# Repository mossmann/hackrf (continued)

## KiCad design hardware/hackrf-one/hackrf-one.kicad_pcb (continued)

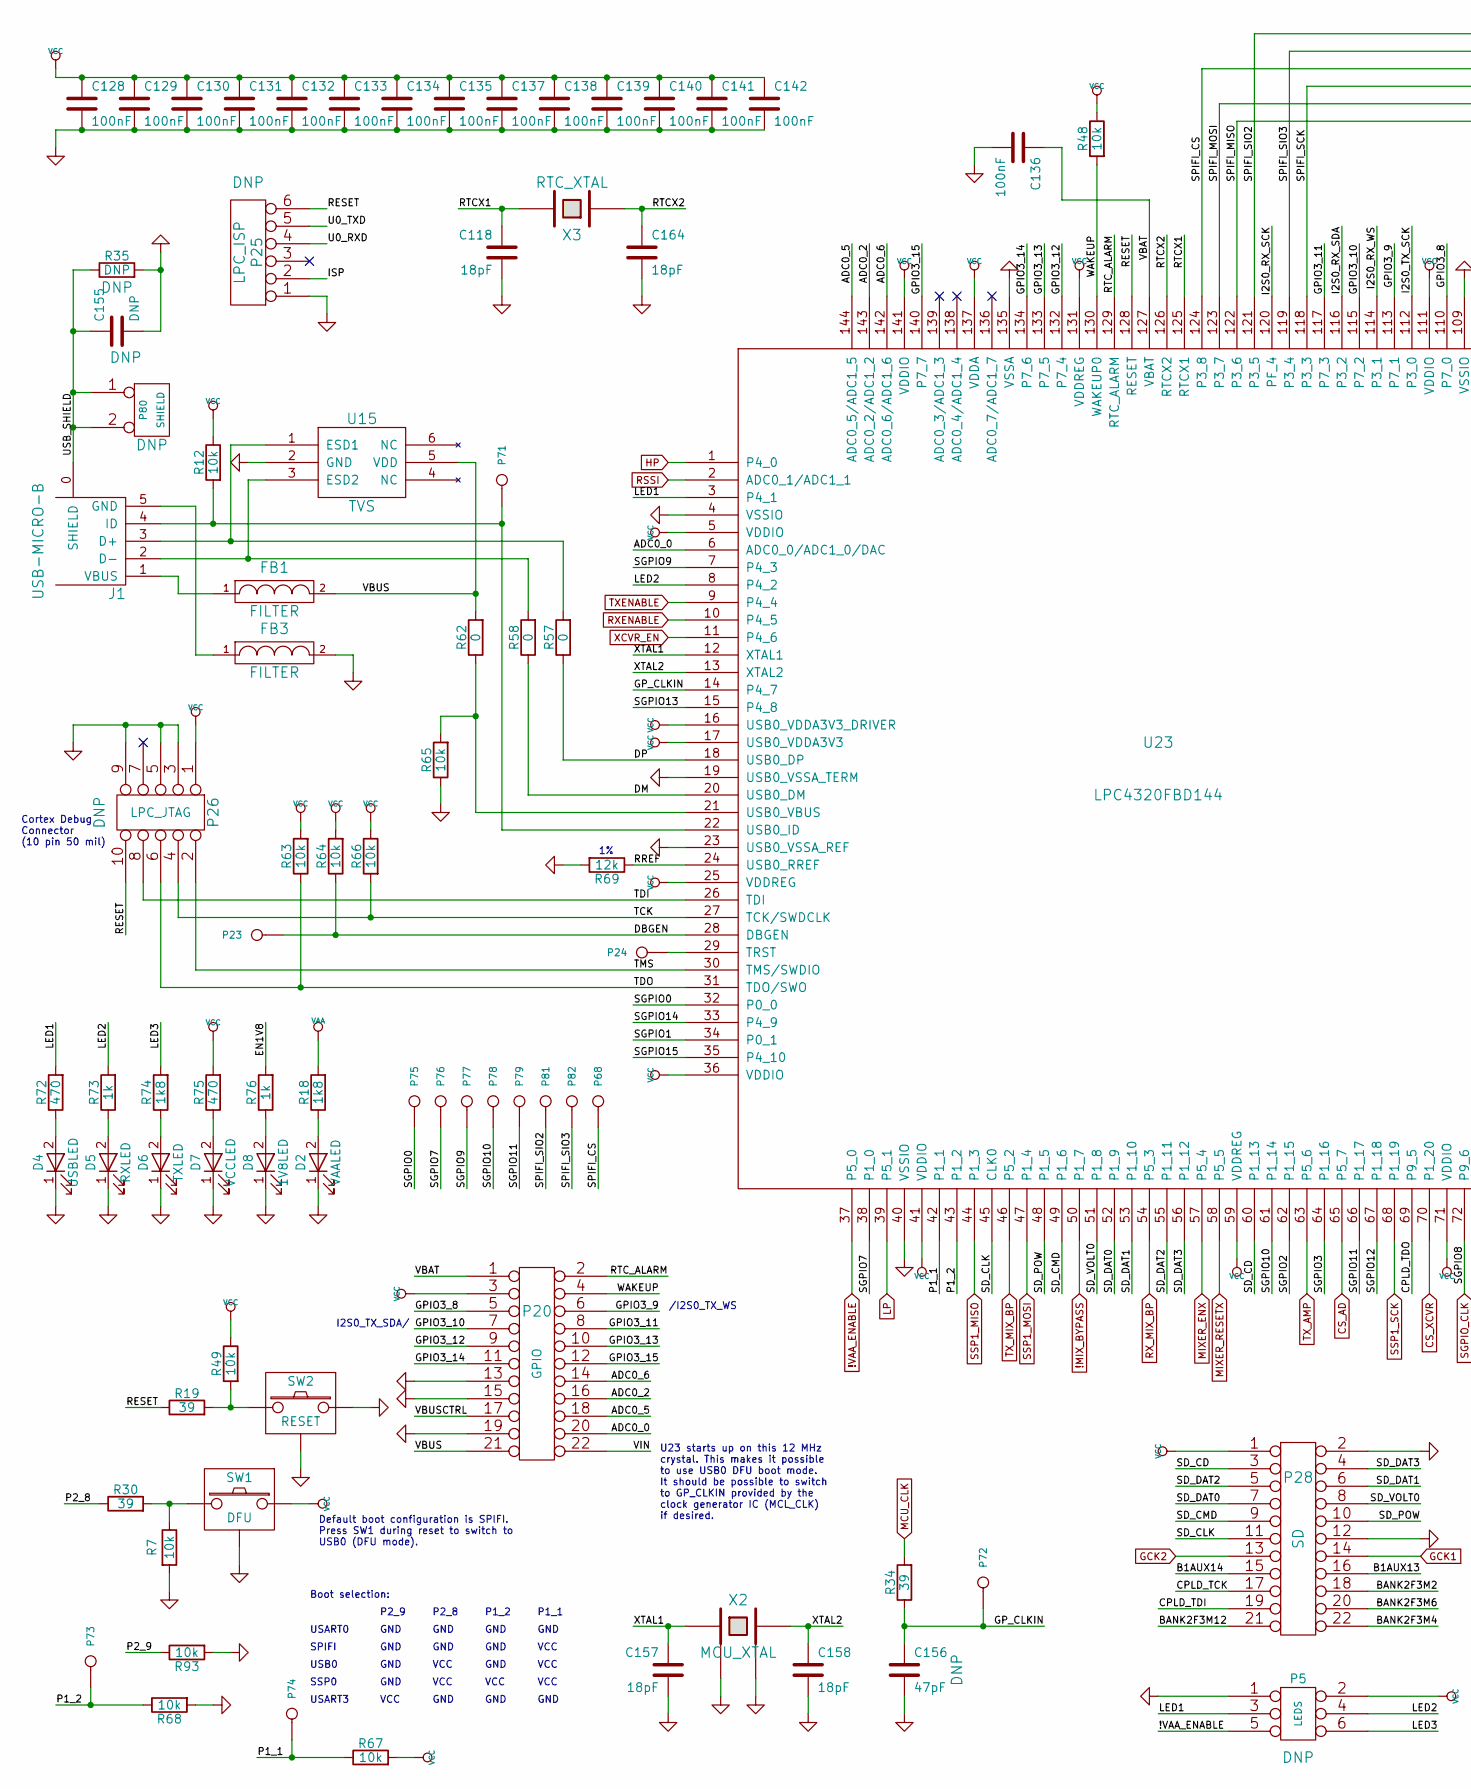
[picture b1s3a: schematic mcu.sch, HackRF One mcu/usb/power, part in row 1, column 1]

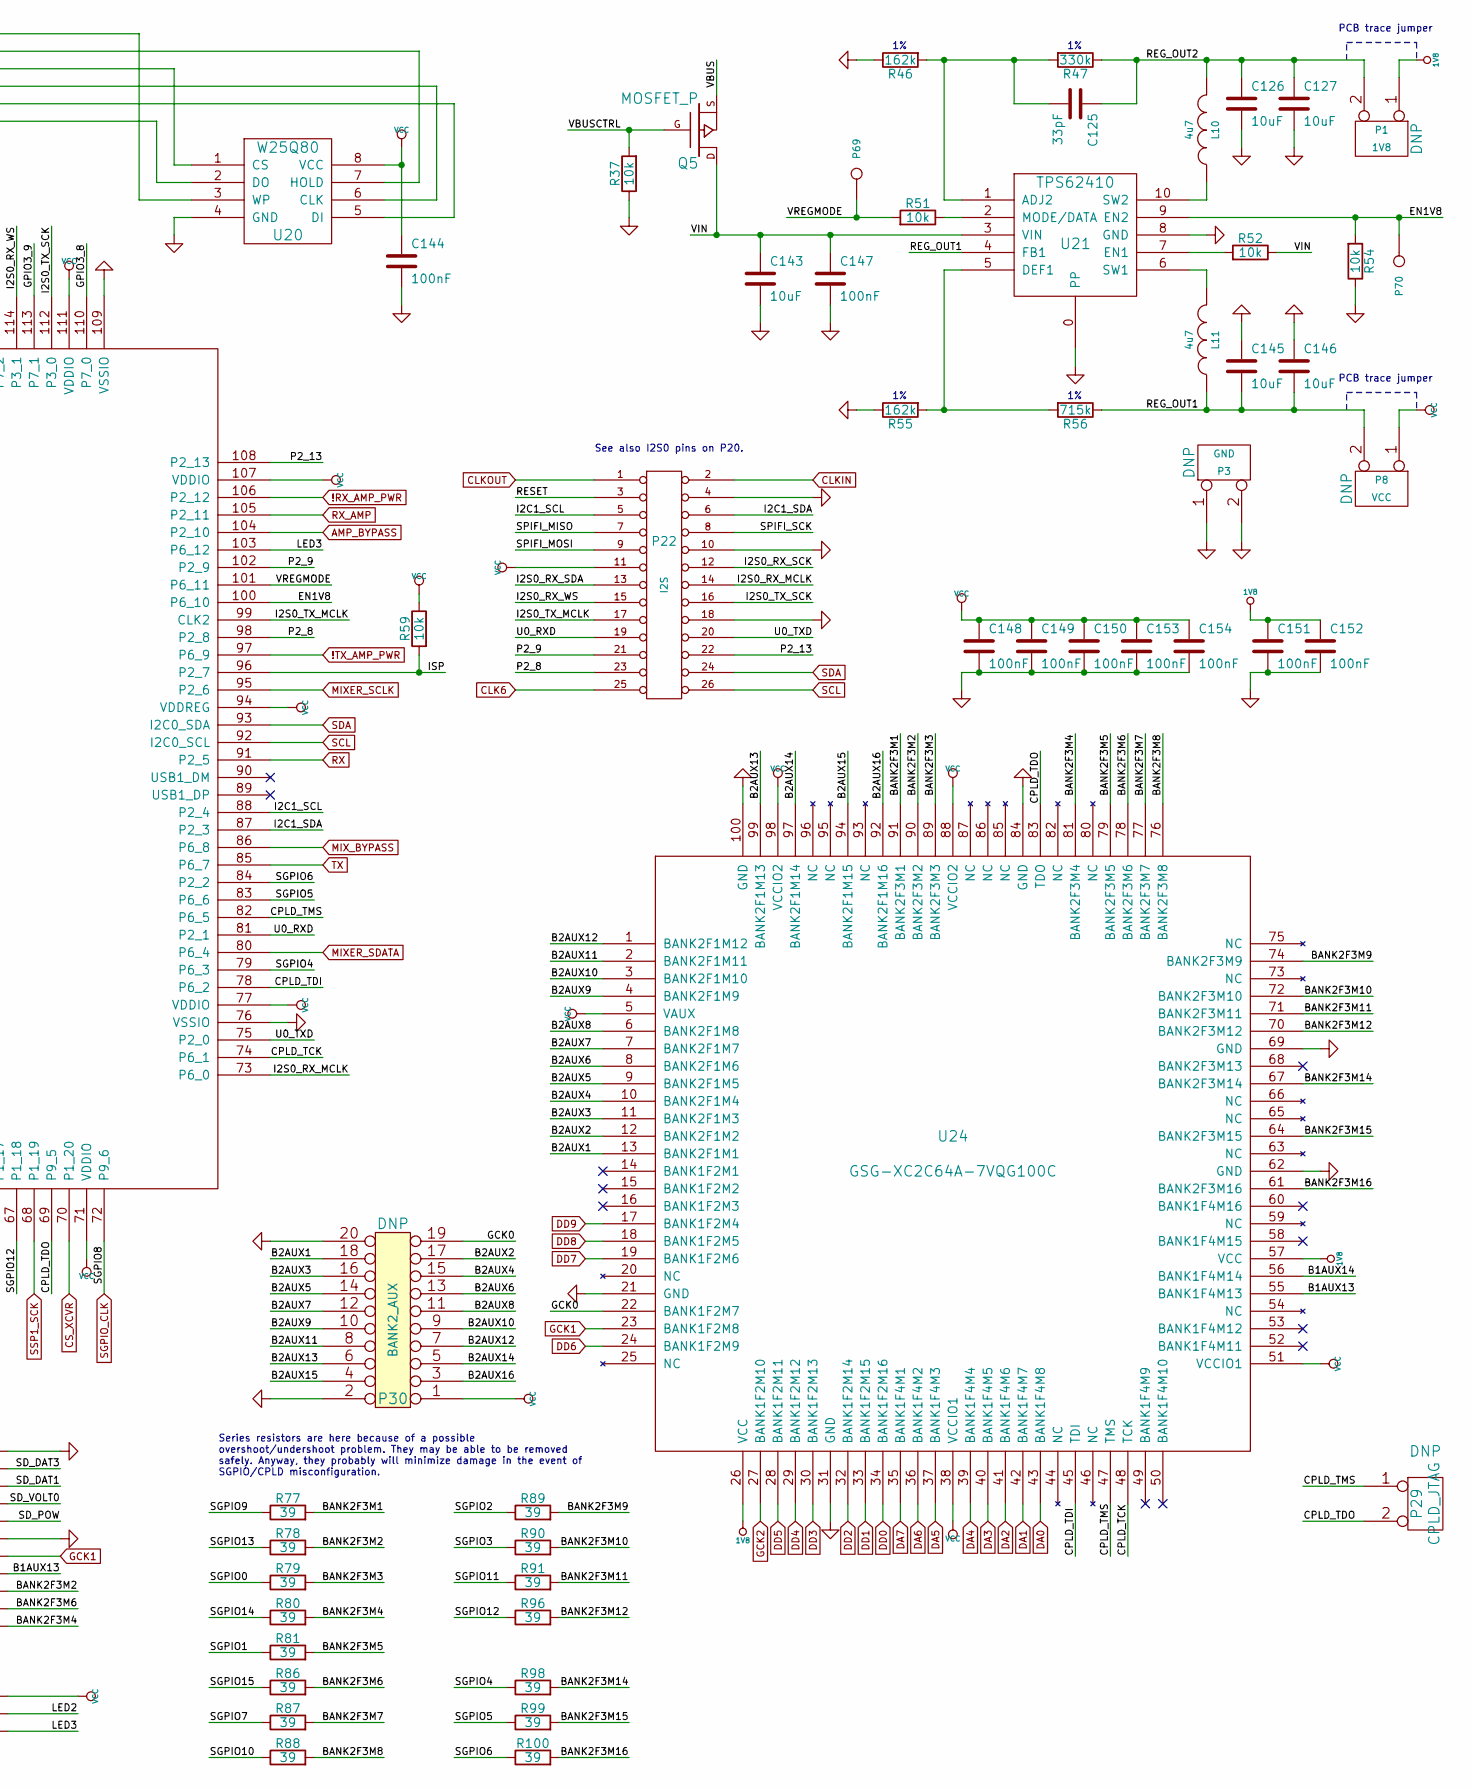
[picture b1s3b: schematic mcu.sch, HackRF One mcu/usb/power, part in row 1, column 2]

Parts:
C118, C157, C158, C164: 18pF; GSG-0402; Part Number GRM1555C1H180JA01D
C125: 33pF; GSG-0402; Part Number GRM1555C1H330JA01D
C126, C127, C143, C145, C146: 10uF; GSG-0805; Part Number GRM21BR61A106KE19L
C128, C129, C130, C131, C132, C133, C134, C135, C136, C137, C138, C139, C140, C141, C142, C144, C147, C148, C149, C150, C151, C152, C153, C154: 100nF; GSG-0402; Part Number GRM155R61A104KA01D
C155: DNP; GSG-0805
C156: 47pF; GSG-0402; Part Number GRM1555C1H470JA01D
D2: VAALED; LTST-S220; Part Number LTST-S220KRKT
D4: USBLED; LTST-S220; Part Number LTST-S220KGKT
D5: RXLED; LTST-S220; Part Number LTST-S220KSKT
D6: TXLED; LTST-S220; Part Number LTST-S220KRKT
D7: VCCLED; LTST-S220; Part Number LTST-S220KGKT
D8: 1V8LED; LTST-S220; Part Number LTST-S220KSKT
FB1, FB3: FILTER; GSG-0805; Part Number BLM21PG221SN1D
J1: USB-MICRO-B; GSG-USB-MICROB-FCI-10103592-EXT; Part Number 10103592-0001LF
L10, L11: 4u7; GSG-NRG4026; Part Number NRG4026T4R7M
P1: 1V8; GSG-HEADER-1x2
P3: GND; GSG-HEADER-NOMARK-1x2
P5: LEDS; GSG-HEADER-2x3
P8: VCC; GSG-HEADER-1x2
P20: GPIO; GSG-HEADER-2x11; Part Number PPPC112LFBN-RC
P22: I2S; GSG-HEADER-2x13; Part Number PPPC132LFBN-RC
P23: DBGEN; GSG-TESTPOINT-50MIL
P24: TRST; GSG-TESTPOINT-50MIL
P25: LPC_ISP; GSG-HEADER-1x6
P26: LPC_JTAG; GSG-50MIL-HEADER-2x5-TH; Part Number GRPB052VWVN-RC
P28: SD; GSG-HEADER-2x11; Part Number PPPC112LFBN-RC
P29: CPLD_JTAG; GSG-HEADER-1x2
P30: BANK2_AUX; GSG-HEADER-2x10
P68: SPIFI_CS; GSG-TESTPOINT-50MIL
P69: VREGMODE; GSG-TESTPOINT-50MIL
P70: EN_1V8; GSG-TESTPOINT-50MIL
P71: ID; GSG-TESTPOINT-50MIL
P72, P75, P76, P77, P78, P79: GP_CLKIN; GSG-TESTPOINT-50MIL
P73: P1_2; GSG-TESTPOINT-50MIL
P74: P1_1; GSG-TESTPOINT-50MIL
P80: SHIELD; GSG-HEADER-NOMARK-1x2
P81: SPIFI_SIO2; GSG-TESTPOINT-50MIL
P82: SPIFI_SIO3; GSG-TESTPOINT-50MIL
Q5: MOSFET_P; SOT23GDS; Part Number AO3407A
R7, R12, R37, R48, R49, R51, R52, R54, R59, R63, R64, R65, R66, R67, R68, R93: 10k; GSG-0402; Part Number RMCF0402JT10K0
R18, R74: 1k8; GSG-0402; Part Number RMCF0402JT1K80
R19, R30, R34, R77, R78, R79, R80, R81, R86, R87, R88, R89, R90, R91, R96, R98, R99, R100: 39; GSG-0402; Part Number RMCF0402JT39R0
R35: DNP; GSG-0805
R46, R55: 162k; GSG-0402; Part Number RMCF0402FT162K
R47: 330k; GSG-0402; Part Number RMCF0402FT330K
R56: 715k; GSG-0402; Part Number RMCF0402FT715K
R57, R58, R62: 0; GSG-0402; Part Number RMCF0402ZT0R00
R69: 12k; GSG-0402; Part Number MCR01MRTF1202
R72, R75: 470; GSG-0402; Part Number RMCF0402JT470R
R73, R76: 1k; GSG-0402; Part Number RMCF0402FT1K00
SW1: DFU; GSG-SWITCH-FSMRA; Part Number FSMRA3JH
SW2: RESET; GSG-SWITCH-FSMRA; Part Number FSMRA3JH
U15: TVS; GSG-LXES1TBCC2-004; Part Number VBUS54CV-HSF-G4-08
U20: W25Q80; GSG-SOIC8-208; Part Number W25Q80DVSSIG
U21: TPS62410; GSG-S-PVSON-N10; Part Number TPS62410DRCR
U23: LPC4320FBD144; GSG-LQFP144; Part Number LPC4320FBD144,551
U24: GSG-XC2C64A-7VQG100C; GSG-VQ100; Part Number XC2C64A-7VQG100C
X2: MCU_XTAL; GSG-XTAL3.2x2.5mm; Part Number 7V-12.000MAAE-T
X3: RTC_XTAL; GSG-XTAL-AB26TRQ; Part Number AB26TRQ-32.768KHZ-T

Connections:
!MIX_BYPASS: U23.50 (P1_7); also elsewhere on the board
!RX_AMP_PWR: U23.106 (P2_12); also elsewhere on the board
!TX_AMP_PWR: U23.97 (P6_9); also elsewhere on the board
!VAA_ENABLE: P5.5, U23.37 (P5_0); also elsewhere on the board
+1.8V: C151.1, C152.1, P1.1, U24.26 (VCC), U24.57 (VCC)
/mcu/usb/power/ADC0_0: P20.20, U23.6 (ADC0_0/ADC1_0/DAC)
/mcu/usb/power/ADC0_2: P20.16, U23.143 (ADC0_2/ADC1_2)
/mcu/usb/power/ADC0_5: P20.18, U23.144 (ADC0_5/ADC1_5)
/mcu/usb/power/ADC0_6: P20.14, U23.142 (ADC0_6/ADC1_6)
/mcu/usb/power/B1AUX13: P28.16, U24.55 (BANK1F4M13)
/mcu/usb/power/B1AUX14: P28.15, U24.56 (BANK1F4M14)
/mcu/usb/power/B2AUX1: P30.18, U24.13 (BANK2F1M1)
/mcu/usb/power/B2AUX2: P30.17, U24.12 (BANK2F1M2)
/mcu/usb/power/B2AUX3: P30.16, U24.11 (BANK2F1M3)
/mcu/usb/power/B2AUX4: P30.15, U24.10 (BANK2F1M4)
/mcu/usb/power/B2AUX5: P30.14, U24.9 (BANK2F1M5)
/mcu/usb/power/B2AUX6: P30.13, U24.8 (BANK2F1M6)
/mcu/usb/power/B2AUX7: P30.12, U24.7 (BANK2F1M7)
/mcu/usb/power/B2AUX8: P30.11, U24.6 (BANK2F1M8)
/mcu/usb/power/B2AUX9: P30.10, U24.4 (BANK2F1M9)
/mcu/usb/power/B2AUX10: P30.9, U24.3 (BANK2F1M10)
/mcu/usb/power/B2AUX11: P30.8, U24.2 (BANK2F1M11)
/mcu/usb/power/B2AUX12: P30.7, U24.1 (BANK2F1M12)
/mcu/usb/power/B2AUX13: P30.6, U24.99 (BANK2F1M13)
/mcu/usb/power/B2AUX14: P30.5, U24.97 (BANK2F1M14)
/mcu/usb/power/B2AUX15: P30.4, U24.94 (BANK2F1M15)
/mcu/usb/power/B2AUX16: P30.3, U24.92 (BANK2F1M16)
/mcu/usb/power/BANK2F3M1: R77.2, U24.91 (BANK2F3M1)
/mcu/usb/power/BANK2F3M2: P28.18, R78.2, U24.90 (BANK2F3M2)
/mcu/usb/power/BANK2F3M3: R79.2, U24.89 (BANK2F3M3)
/mcu/usb/power/BANK2F3M4: P28.22, R80.2, U24.81 (BANK2F3M4)
/mcu/usb/power/BANK2F3M5: R81.2, U24.79 (BANK2F3M5)
/mcu/usb/power/BANK2F3M6: P28.20, R86.2, U24.78 (BANK2F3M6)
/mcu/usb/power/BANK2F3M7: R87.2, U24.77 (BANK2F3M7)
/mcu/usb/power/BANK2F3M8: R88.2, U24.76 (BANK2F3M8)
/mcu/usb/power/BANK2F3M9: R89.2, U24.74 (BANK2F3M9)
/mcu/usb/power/BANK2F3M10: R90.2, U24.72 (BANK2F3M10)
/mcu/usb/power/BANK2F3M11: R91.2, U24.71 (BANK2F3M11)
/mcu/usb/power/BANK2F3M12: P28.21, R96.2, U24.70 (BANK2F3M12)
/mcu/usb/power/BANK2F3M14: R98.2, U24.67 (BANK2F3M14)
/mcu/usb/power/BANK2F3M15: R99.2, U24.64 (BANK2F3M15)
/mcu/usb/power/BANK2F3M16: R100.2, U24.61 (BANK2F3M16)
/mcu/usb/power/CPLD_TCK: P28.17, U23.74 (P6_1), U24.48 (TCK)
/mcu/usb/power/CPLD_TDI: P28.19, U23.78 (P6_2), U24.45 (TDI)
/mcu/usb/power/CPLD_TDO: P29.2 (PM), U23.69 (P9_5), U24.83 (TDO)
/mcu/usb/power/CPLD_TMS: P29.1, U23.82 (P6_5), U24.47 (TMS)
/mcu/usb/power/DBGEN: P23.1, R64.1, U23.28 (DBGEN)
/mcu/usb/power/DM: R58.1, U23.20 (USB0_DM)
/mcu/usb/power/DP: R57.1, U23.18 (USB0_DP)
/mcu/usb/power/EN1V8: P70.1, R54.2, R76.2, U21.9 (EN2), U23.100 (P6_10)
/mcu/usb/power/GCK0: P30.19, U24.22 (BANK1F2M7)
/mcu/usb/power/GPIO3_8: P20.5, U23.110 (P7_0)
/mcu/usb/power/GPIO3_9: P20.6, U23.113 (P7_1)
/mcu/usb/power/GPIO3_10: P20.7, U23.115 (P7_2)
/mcu/usb/power/GPIO3_11: P20.8, U23.117 (P7_3)
/mcu/usb/power/GPIO3_12: P20.9, U23.132 (P7_4)
/mcu/usb/power/GPIO3_13: P20.10, U23.133 (P7_5)
/mcu/usb/power/GPIO3_14: P20.11, U23.134 (P7_6)
/mcu/usb/power/GPIO3_15: P20.12, U23.140 (P7_7)
/mcu/usb/power/GP_CLKIN: C156.1, P72.1, R34.1, U23.14 (P4_7)
/mcu/usb/power/I2C1_SCL: P22.5, U23.88 (P2_4)
/mcu/usb/power/I2C1_SDA: P22.6, U23.87 (P2_3)
/mcu/usb/power/I2S0_RX_MCLK: P22.14, U23.73 (P6_0)
/mcu/usb/power/I2S0_RX_SCK: P22.12, U23.120 (PF_4)
/mcu/usb/power/I2S0_RX_SDA: P22.13, U23.116 (P3_2)
/mcu/usb/power/I2S0_RX_WS: P22.15, U23.114 (P3_1)
/mcu/usb/power/I2S0_TX_MCLK: P22.17, U23.99 (CLK2)
/mcu/usb/power/I2S0_TX_SCK: P22.16, U23.112 (P3_0)
/mcu/usb/power/ISP: P25.2, R59.2, U23.96 (P2_7)
/mcu/usb/power/LED1: P5.3, R72.2, U23.3 (P4_1)
/mcu/usb/power/LED2: P5.4, R73.2, U23.8 (P4_2)
/mcu/usb/power/LED3: P5.6, R74.2, U23.103 (P6_12)
/mcu/usb/power/P1_1: P74.1, R67.1, U23.42 (P1_1)
/mcu/usb/power/P1_2: P73.1, R68.1, U23.43 (P1_2)
/mcu/usb/power/P2_8: P22.23, R30.1, U23.98 (P2_8)
/mcu/usb/power/P2_9: P22.21, R93.1, U23.102 (P2_9)
/mcu/usb/power/P2_13: P22.22, U23.108 (P2_13)
/mcu/usb/power/REG_OUT1: C145.2, C146.2, L11.1, P8.2 (PM), R56.1, U21.4 (FB1)
/mcu/usb/power/REG_OUT2: C125.1, C126.1, C127.1, L10.2, P1.2 (PM), R47.1
/mcu/usb/power/RESET: P22.3, P25.6, P26.10, R19.1, U23.128 (RESET)
/mcu/usb/power/RREF: R69.1, U23.24 (USB0_RREF)
/mcu/usb/power/RTCX1: C118.1, U23.125 (RTCX1), X3.2
/mcu/usb/power/RTCX2: C164.1, U23.126 (RTCX2), X3.1
/mcu/usb/power/RTC_ALARM: P20.2, U23.129 (RTC_ALARM)
/mcu/usb/power/SD_CD: P28.3, U23.60 (P1_13)
/mcu/usb/power/SD_CLK: P28.11, U23.45 (CLK0)
/mcu/usb/power/SD_CMD: P28.9, U23.49 (P1_6)
/mcu/usb/power/SD_DAT0: P28.7, U23.52 (P1_9)
/mcu/usb/power/SD_DAT1: P28.6, U23.53 (P1_10)
/mcu/usb/power/SD_DAT2: P28.5, U23.55 (P1_11)
/mcu/usb/power/SD_DAT3: P28.4, U23.56 (P1_12)
/mcu/usb/power/SD_POW: P28.10, U23.48 (P1_5)
/mcu/usb/power/SD_VOLT0: P28.8, U23.51 (P1_8)
/mcu/usb/power/SGPIO0: P75.1, R79.1, U23.32 (P0_0)
/mcu/usb/power/SGPIO1: R81.1, U23.34 (P0_1)
/mcu/usb/power/SGPIO2: R89.1, U23.62 (P1_15)
/mcu/usb/power/SGPIO3: R90.1, U23.64 (P1_16)
/mcu/usb/power/SGPIO4: R98.1, U23.79 (P6_3)
/mcu/usb/power/SGPIO5: R99.1, U23.83 (P6_6)
/mcu/usb/power/SGPIO6: R100.1, U23.84 (P2_2)
/mcu/usb/power/SGPIO7: P76.1, R87.1, U23.38 (P1_0)
/mcu/usb/power/SGPIO9: P77.1, R77.1, U23.7 (P4_3)
/mcu/usb/power/SGPIO10: P78.1, R88.1, U23.61 (P1_14)
/mcu/usb/power/SGPIO11: P79.1, R91.1, U23.66 (P1_17)
/mcu/usb/power/SGPIO12: R96.1, U23.67 (P1_18)
/mcu/usb/power/SGPIO13: R78.1, U23.15 (P4_8)
/mcu/usb/power/SGPIO14: R80.1, U23.33 (P4_9)
/mcu/usb/power/SGPIO15: R86.1, U23.35 (P4_10)
/mcu/usb/power/SPIFI_CS: P68.1, U20.1 (CS), U23.124 (P3_8)
/mcu/usb/power/SPIFI_MISO: P22.7, U20.2 (DO), U23.122 (P3_6)
/mcu/usb/power/SPIFI_MOSI: P22.9, U20.5 (DI), U23.123 (P3_7)
/mcu/usb/power/SPIFI_SCK: P22.8, U20.6 (CLK), U23.118 (P3_3)
/mcu/usb/power/SPIFI_SIO2: P81.1, U20.3 (WP), U23.121 (P3_5)
/mcu/usb/power/SPIFI_SIO3: P82.1, U20.7 (HOLD), U23.119 (P3_4)
/mcu/usb/power/TCK: P26.4, R66.2, U23.27 (TCK/SWDCLK)
/mcu/usb/power/TDI: P26.8, U23.26 (TDI)
/mcu/usb/power/TDO: P26.6, R63.1, U23.31 (TDO/SWO)
/mcu/usb/power/TMS: P26.2, U23.30 (TMS/SWDIO)
/mcu/usb/power/U0_RXD: P22.19, P25.4, U23.81 (P2_1)
/mcu/usb/power/U0_TXD: P22.20, P25.5, U23.75 (P2_0)
/mcu/usb/power/USB_SHIELD: C155.1, J1.0 (SHIELD), P80.1, P80.2 (PM), R35.1
/mcu/usb/power/VBAT: C136.1, P20.1, U23.127 (VBAT)
/mcu/usb/power/VBUS: FB1.2, P20.21, Q5.S, R62.2, U15.5 (VDD)
/mcu/usb/power/VBUSCTRL: P20.17, Q5.G, R37.2
/mcu/usb/power/VIN: C143.1, C147.1, P20.22, Q5.D, R52.1, U21.3 (VIN)
/mcu/usb/power/VREGMODE: P69.1, R51.2, U23.101 (P6_11)
/mcu/usb/power/WAKEUP: P20.4, R48.2, U23.130 (WAKEUP0)
/mcu/usb/power/XTAL1: C157.1, U23.12 (XTAL1), X2.1
/mcu/usb/power/XTAL2: C158.1, U23.13 (XTAL2), X2.3
AMP_BYPASS: U23.104 (P2_10); also elsewhere on the board
CLK6: P22.25 (P24); also elsewhere on the board
CLKIN: P22.2; also elsewhere on the board
CLKOUT: P22.1; also elsewhere on the board
CS_AD: U23.65 (P5_7); also elsewhere on the board
CS_XCVR: U23.70 (P1_20); also elsewhere on the board
DA0: U24.43 (BANK1F4M8); also elsewhere on the board
DA1: U24.42 (BANK1F4M7); also elsewhere on the board
DA2: U24.41 (BANK1F4M6); also elsewhere on the board
DA3: U24.40 (BANK1F4M5); also elsewhere on the board
DA4: U24.39 (BANK1F4M4); also elsewhere on the board
DA5: U24.37 (BANK1F4M3); also elsewhere on the board
DA6: U24.36 (BANK1F4M2); also elsewhere on the board
DA7: U24.35 (BANK1F4M1); also elsewhere on the board
DD0: U24.34 (BANK1F2M16); also elsewhere on the board
DD1: U24.33 (BANK1F2M15); also elsewhere on the board
DD2: U24.32 (BANK1F2M14); also elsewhere on the board
DD3: U24.30 (BANK1F2M13); also elsewhere on the board
DD4: U24.29 (BANK1F2M12); also elsewhere on the board
DD5: U24.28 (BANK1F2M11); also elsewhere on the board
DD6: U24.24 (BANK1F2M9); also elsewhere on the board
DD7: U24.19 (BANK1F2M6); also elsewhere on the board
DD8: U24.18 (BANK1F2M5); also elsewhere on the board
DD9: U24.17 (BANK1F2M4); also elsewhere on the board
GCK1: P28.14, U24.23 (BANK1F2M8); also elsewhere on the board
GCK2: P28.13, U24.27 (BANK1F2M10); also elsewhere on the board
GND: C118.2, C126.2, C127.2, C128.2, C129.2, C130.2, C131.2, C132.2, C133.2, C134.2, C135.2, C136.2, C137.2, C138.2, C139.2, C140.2, C141.2, C142.2, C143.2, C144.2, C145.1, C146.1, C147.2, C148.2, C149.2, C150.2, C151.2, C152.2, C153.2, C154.2, C155.2, C156.2, C157.2, C158.2, C164.2, D2.1 (K), D4.1 (K), D5.1 (K), D6.1 (K), D7.1 (K), D8.1 (K), FB3.2, P3.1, P3.2 (PM), P5.1, P20.13, P20.15, P20.19, P22.4, P22.10, P22.18, P25.1, P26.3, P26.5, P26.9, P28.2, P28.12, P30.2, P30.20, R7.2, R35.2, R37.1, R46.1, R54.1, R55.1, R65.1, R68.2, R69.2, R93.2, SW1.0 (SHIELD), SW2.0 (SHIELD), SW2.1, U15.2 (GND), U20.4 (GND), U21.0 (PP), U21.8 (GND), U23.4 (VSSIO), U23.19 (USB0_VSSA_TERM), U23.23 (USB0_VSSA_REF), U23.40 (VSSIO), U23.76 (VSSIO), U23.109 (VSSIO), U23.135 (VSSA), U24.21 (GND), U24.31 (GND), U24.62 (GND), U24.69 (GND), U24.84 (GND), U24.100 (GND), X2.2, X2.4; also elsewhere on the board
HP: U23.1 (P4_0); also elsewhere on the board
LP: U23.39 (P5_1); also elsewhere on the board
MCU_CLK: R34.2; also elsewhere on the board
MIXER_ENX: U23.57 (P5_4); also elsewhere on the board
MIXER_RESETX: U23.58 (P5_5); also elsewhere on the board
MIXER_SCLK: U23.95 (P2_6); also elsewhere on the board
MIXER_SDATA: U23.80 (P6_4); also elsewhere on the board
MIX_BYPASS: U23.86 (P6_8); also elsewhere on the board
unnamed: C125.2, R46.2, R47.2, U21.1 (ADJ2)
unnamed: D2.2 (A), R18.1
unnamed: D4.2 (A), R72.1
unnamed: D5.2 (A), R73.1
unnamed: D6.2 (A), R74.1
unnamed: D7.2 (A), R75.1
unnamed: D8.2 (A), R76.1
unnamed: FB1.1, J1.1 (VBUS)
unnamed: FB3.1, J1.5 (GND)
unnamed: J1.2 (D-), R58.2, U15.3 (ESD2)
unnamed: J1.3 (D+), R57.2, U15.1 (ESD1)
unnamed: J1.4 (ID), P71.1, R12.2, U23.22 (USB0_ID)
unnamed: L10.1, U21.10 (SW2)
unnamed: L11.2, U21.6 (SW1)
unnamed: P24.1, U23.29 (TRST)
unnamed: R19.2, R49.2, SW2.2
unnamed: R7.1, R30.2, SW1.2
unnamed: R51.1, U21.2 (MODE/DATA)
unnamed: R52.2, U21.7 (EN1)
unnamed: R55.2, R56.2, U21.5 (DEF1)
unnamed: R62.1, R65.2, U23.21 (USB0_VBUS)
RSSI: U23.2 (ADC0_1/ADC1_1); also elsewhere on the board
RX: U23.91 (P2_5); also elsewhere on the board
RXENABLE: U23.10 (P4_5); also elsewhere on the board
RX_AMP: U23.105 (P2_11); also elsewhere on the board
RX_MIX_BP: U23.54 (P5_3); also elsewhere on the board
SCL: P22.26 (P22), U23.92 (I2C0_SCL); also elsewhere on the board
SDA: P22.24 (P20), U23.93 (I2C0_SDA); also elsewhere on the board
SGPIO_CLK: U23.72 (P9_6); also elsewhere on the board
SSP1_MISO: U23.44 (P1_3); also elsewhere on the board
SSP1_MOSI: U23.47 (P1_4); also elsewhere on the board
SSP1_SCK: U23.68 (P1_19); also elsewhere on the board
TX: U23.85 (P6_7); also elsewhere on the board
TXENABLE: U23.9 (P4_4); also elsewhere on the board
TX_AMP: U23.63 (P5_6); also elsewhere on the board
TX_MIX_BP: U23.46 (P5_2); also elsewhere on the board
VAA: R18.2; also elsewhere on the board
VCC: C128.1, C129.1, C130.1, C131.1, C132.1, C133.1, C134.1, C135.1, C137.1, C138.1, C139.1, C140.1, C141.1, C142.1, C144.1, C148.1, C149.1, C150.1, C153.1, C154.1, P5.2, P8.1, P20.3, P22.11, P26.1, P28.1, P30.1, R12.1, R48.1, R49.1, R59.1, R63.2, R64.2, R66.1, R67.2, R75.2, SW1.1, U20.8 (VCC), U23.5 (VDDIO), U23.16 (USB0_VDDA3V3_DRIVER), U23.17 (USB0_VDDA3V3), U23.25 (VDDREG), U23.36 (VDDIO), U23.41 (VDDIO), U23.59 (VDDREG), U23.71 (VDDIO), U23.77 (VDDIO), U23.94 (VDDREG), U23.107 (VDDIO), U23.111 (VDDIO), U23.131 (VDDREG), U23.137 (VDDA), U23.141 (VDDIO), U24.5 (VAUX), U24.38 (VCCIO1), U24.51 (VCCIO1), U24.88 (VCCIO2), U24.98 (VCCIO2); also elsewhere on the board
XCVR_EN: U23.11 (P4_6); also elsewhere on the board

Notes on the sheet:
Cortex Debug Connector (10 pin 50 mil)
U23 starts up on this 12 MHz crystal. This makes it possible to use USB0 DFU boot mode. It should be possible to switch to GP_CLKIN provided by the clock generator IC (MCL_CLK) if desired.
GND
VCC
P1_1
P1_2
P2_8
P2_9
USART3
SSP0
USB0
SPIFI
USART0
Boot selection:
Default boot configuration is SPIFI. Press SW1 during reset to switch to USB0 (DFU mode).
Series resistors are here because of a possible overshoot/undershoot problem. They may be able to be removed safely. Anyway, they probably will minimize damage in the event of SGPIO/CPLD misconfiguration.
/I2S0_TX_WS
I2S0_TX_SDA/
See also I2S0 pins on P20.
PCB trace jumper

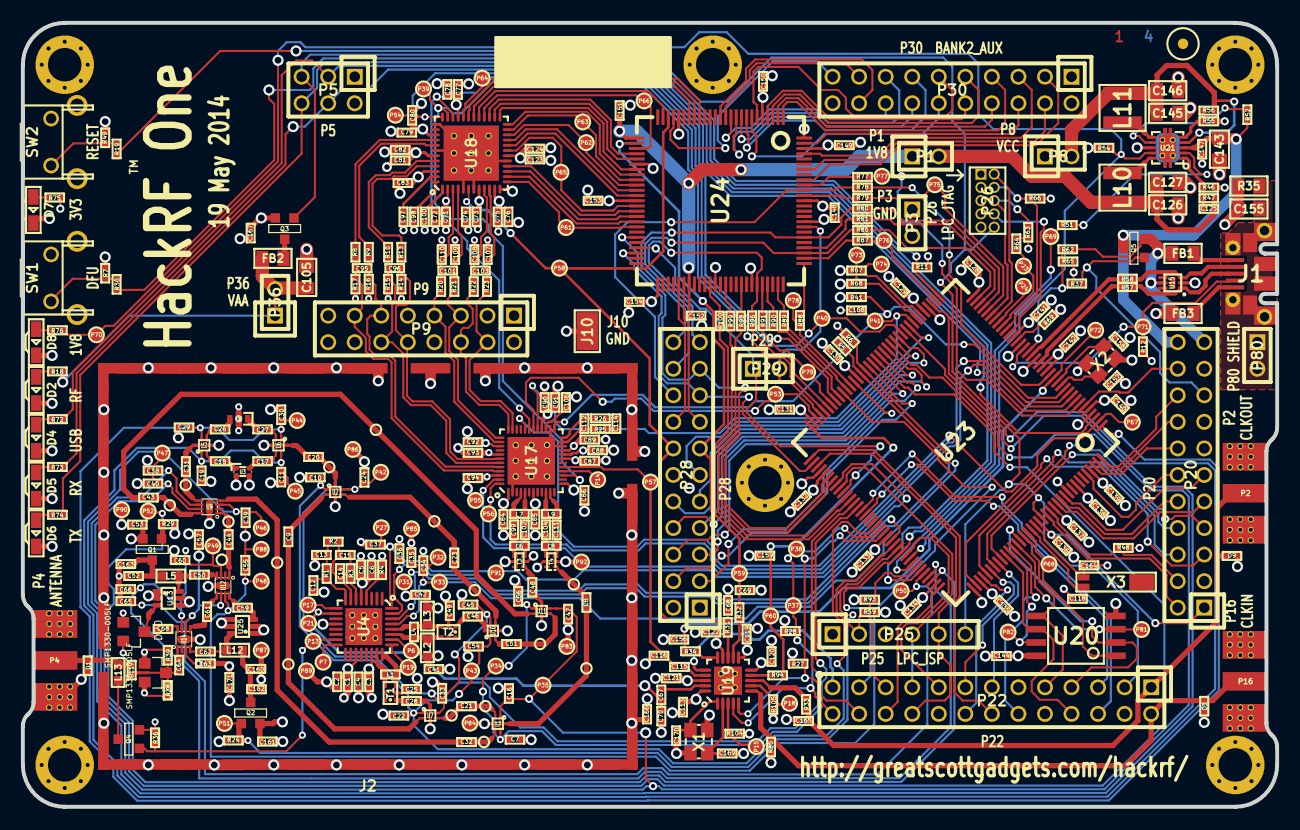
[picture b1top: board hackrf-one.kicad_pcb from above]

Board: 4 copper layers, 120.0 x 75.0 mm, 436 parts (0 on the bottom side), 317 nets.

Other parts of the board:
MARK1MM: VAL**; GSG-MARK1MM
TESTPOINT-30MIL-MASKONLY, TESTPOINT-30MIL-MASKONLY#2, TESTPOINT-30MIL-MASKONLY#3, TESTPOINT-30MIL-MASKONLY#4, TESTPOINT-30MIL-MASKONLY#5, TESTPOINT-30MIL-MASKONLY#6, TESTPOINT-30MIL-MASKONLY#7, TESTPOINT-30MIL-MASKONLY#8, TESTPOINT-30MIL-MASKONLY#9, TESTPOINT-30MIL-MASKONLY#10, TESTPOINT-30MIL-MASKONLY#11, TESTPOINT-30MIL-MASKONLY#12, TESTPOINT-30MIL-MASKONLY#13, TESTPOINT-30MIL-MASKONLY#14, TESTPOINT-30MIL-MASKONLY#15, TESTPOINT-30MIL-MASKONLY#16: VAL**; GSG-TESTPOINT-30MIL-MASKONLY

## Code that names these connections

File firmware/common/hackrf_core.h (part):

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 */

/* GPIO Output PinMux */
#define SCU_PINMUX_LED1     (P4_1)  /* GPIO2[1] on P4_1 */
#define SCU_PINMUX_LED2     (P4_2)  /* GPIO2[2] on P4_2 */
#define SCU_PINMUX_LED3     (P6_12) /* GPIO2[8] on P6_12 */
#ifdef RAD1O
#define SCU_PINMUX_LED4     (PB_6) /* GPIO5[26] on PB_6 */
#endif

#define SCU_PINMUX_EN1V8    (P6_10) /* GPIO3[6] on P6_10 */

/* GPIO Input PinMux */
#define SCU_PINMUX_BOOT0    (P1_1)  /* GPIO0[8] on P1_1 */
#define SCU_PINMUX_BOOT1    (P1_2)  /* GPIO0[9] on P1_2 */
#define SCU_PINMUX_BOOT2    (P2_8)  /* GPIO5[7] on P2_8 */
#define SCU_PINMUX_BOOT3    (P2_9)  /* GPIO1[10] on P2_9 */

/* USB peripheral */
#ifdef JAWBREAKER
#define SCU_PINMUX_USB_LED0 (P6_8)
#define SCU_PINMUX_USB_LED1 (P6_7)
#endif

/* SSP1 Peripheral PinMux */
#define SCU_SSP1_MISO       (P1_3)  /* P1_3 */
#define SCU_SSP1_MOSI       (P1_4)  /* P1_4 */
#define SCU_SSP1_SCK        (P1_19) /* P1_19 */
#define SCU_SSP1_SSEL       (P1_20) /* P1_20 */

/* CPLD JTAG interface */
#define SCU_PINMUX_CPLD_TDO (P9_5)  /* GPIO5[18] */
#define SCU_PINMUX_CPLD_TCK (P6_1)  /* GPIO3[ 0] */
#if (defined HACKRF_ONE || defined RAD1O)
#define SCU_PINMUX_CPLD_TMS (P6_5)  /* GPIO3[ 4] */
#define SCU_PINMUX_CPLD_TDI (P6_2)  /* GPIO3[ 1] */
#else
#define SCU_PINMUX_CPLD_TMS (P6_2)  /* GPIO3[ 1] */
#define SCU_PINMUX_CPLD_TDI (P6_5)  /* GPIO3[ 4] */
#endif

/* CPLD SGPIO interface */
#define SCU_PINMUX_SGPIO0   (P0_0)
#define SCU_PINMUX_SGPIO1   (P0_1)
#define SCU_PINMUX_SGPIO2   (P1_15)
#define SCU_PINMUX_SGPIO3   (P1_16)
#define SCU_PINMUX_SGPIO4   (P6_3)
#define SCU_PINMUX_SGPIO5   (P6_6)
#define SCU_PINMUX_SGPIO6   (P2_2)
#define SCU_PINMUX_SGPIO7   (P1_0)
#if (defined JAWBREAKER || defined HACKRF_ONE || defined RAD1O)
#define SCU_PINMUX_SGPIO8   (P9_6)
#endif
#define SCU_PINMUX_SGPIO9   (P4_3)
#define SCU_PINMUX_SGPIO10  (P1_14)
#define SCU_PINMUX_SGPIO11  (P1_17)
#define SCU_PINMUX_SGPIO12  (P1_18)
#define SCU_PINMUX_SGPIO13  (P4_8)
#define SCU_PINMUX_SGPIO14  (P4_9)
#define SCU_PINMUX_SGPIO15  (P4_10)

/* MAX2837 GPIO (XCVR_CTL) PinMux */
#ifdef RAD1O
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#define SCU_XCVR_B7         (P9_3)  /* GPIO[] on P8_3 */
#endif

#define SCU_XCVR_ENABLE     (P4_6)  /* GPIO2[6] on P4_6 */
#define SCU_XCVR_RXENABLE   (P4_5)  /* GPIO2[5] on P4_5 */
#define SCU_XCVR_TXENABLE   (P4_4)  /* GPIO2[4] on P4_4 */
#define SCU_XCVR_CS         (P1_20) /* GPIO0[15] on P1_20 */

/* MAX5864 SPI chip select (AD_CS) GPIO PinMux */
#define SCU_AD_CS           (P5_7)  /* GPIO2[7] on P5_7 */

/* RFFC5071 GPIO serial interface PinMux */
#if (defined JAWBREAKER || defined HACKRF_ONE)
#define SCU_MIXER_ENX       (P5_4)  /* GPIO2[13] on P5_4 */
#define SCU_MIXER_SCLK      (P2_6)  /* GPIO5[6] on P2_6 */
#define SCU_MIXER_SDATA     (P6_4)  /* GPIO3[3] on P6_4 */
#define SCU_MIXER_RESETX    (P5_5)  /* GPIO2[14] on P5_5 */
#endif
#ifdef RAD1O
#define SCU_VCO_CE          (P5_4)  /* GPIO2[13] on P5_4 */
#define SCU_VCO_SCLK        (P2_6)  /* GPIO5[6] on P2_6 */
#define SCU_VCO_SDATA       (P6_4)  /* GPIO3[3] on P6_4 */
#define SCU_VCO_LE          (P5_5)  /* GPIO2[14] on P5_5 */
#define SCU_VCO_MUX         (PB_5)  /* GPIO5[25] on PB_5 */
#define SCU_MIXER_EN        (P6_8)  /* GPIO5[16] on P6_8 */
#define SCU_SYNT_RFOUT_EN   (P6_9)  /* GPIO3[5] on P6_9 */
#endif

/* RF LDO control */
#ifdef JAWBREAKER
#define SCU_RF_LDO_ENABLE   (P5_0)  /* GPIO2[9] on P5_0 */
#endif

/* RF supply (VAA) control */
#ifdef HACKRF_ONE
#define SCU_NO_VAA_ENABLE   (P5_0)  /* GPIO2[9] on P5_0 */
#endif
#ifdef RAD1O
#define SCU_VAA_ENABLE      (P5_0)  /* GPIO2[9] on P5_0 */
#endif


/* SPI flash */
#define SCU_SSP0_MISO       (P3_6)
#define SCU_SSP0_MOSI       (P3_7)
#define SCU_SSP0_SCK        (P3_3)
#define SCU_SSP0_SSEL       (P3_8) /* GPIO5[11] on P3_8 */
#define SCU_FLASH_HOLD      (P3_4) /* GPIO1[14] on P3_4 */
#define SCU_FLASH_WP        (P3_5) /* GPIO1[15] on P3_5 */

/* RF switch control */
#ifdef HACKRF_ONE
#define SCU_HP              (P4_0)  /* GPIO2[0] on P4_0 */
#define SCU_LP              (P5_1)  /* GPIO2[10] on P5_1 */
#define SCU_TX_MIX_BP       (P5_2)  /* GPIO2[11] on P5_2 */
#define SCU_NO_MIX_BYPASS   (P1_7)  /* GPIO1[0] on P1_7 */
#define SCU_RX_MIX_BP       (P5_3)  /* GPIO2[12] on P5_3 */
#define SCU_TX_AMP          (P5_6)  /* GPIO2[15] on P5_6 */
#define SCU_TX              (P6_7)  /* GPIO5[15] on P6_7 */
#define SCU_MIX_BYPASS      (P6_8)  /* GPIO5[16] on P6_8 */
#define SCU_RX              (P2_5)  /* GPIO5[5] on P2_5 */
#define SCU_NO_TX_AMP_PWR   (P6_9)  /* GPIO3[5] on P6_9 */
#define SCU_AMP_BYPASS      (P2_10) /* GPIO0[14] on P2_10 */
#define SCU_RX_AMP          (P2_11) /* GPIO1[11] on P2_11 */
#define SCU_NO_RX_AMP_PWR   (P2_12) /* GPIO1[12] on P2_12 */
#endif
#ifdef RAD1O
#define SCU_BY_AMP          (P1_7)  /* GPIO1[0] on P1_7 */
#define SCU_BY_AMP_N        (P2_5)  /* GPIO5[5] on P2_5 */
#define SCU_TX_RX           (P2_10) /* GPIO0[14] on P2_10 */
#define SCU_TX_RX_N         (P2_11) /* GPIO1[11] on P2_11 */
#define SCU_BY_MIX          (P2_12) /* GPIO1[12] on P2_12 */
#define SCU_BY_MIX_N        (P5_1) /* GPIO2[10] on P5_1 */
#define SCU_LOW_HIGH_FILT   (P5_2) /* GPIO2[11] on P5_2 */
#define SCU_LOW_HIGH_FILT_N (P5_3) /* GPIO2[12] on P5_3 */
#define SCU_TX_AMP          (P5_6) /* GPIO2[15] on P5_6 */
#define SCU_RX_LNA          (P6_7) /* GPIO5[15] on P6_7 */
#endif

/* TODO add other Pins */
#define SCU_PINMUX_GPIO3_8  (P7_0)  /* GPIO3[8] */
#define SCU_PINMUX_GPIO3_9  (P7_1)  /* GPIO3[9] */
#define SCU_PINMUX_GPIO3_10 (P7_2)  /* GPIO3[10] */
#define SCU_PINMUX_GPIO3_11 (P7_3)  /* GPIO3[11] */
#define SCU_PINMUX_GPIO3_12 (P7_4)  /* GPIO3[12] */
#define SCU_PINMUX_GPIO3_13 (P7_5)  /* GPIO3[13] */
#define SCU_PINMUX_GPIO3_14 (P7_6)  /* GPIO3[14] */
#define SCU_PINMUX_GPIO3_15 (P7_7)  /* GPIO3[15] */

#define SCU_PINMUX_SD_POW   (P1_5)  /* GPIO1[8] */
#define SCU_PINMUX_SD_CMD   (P1_6)  /* GPIO1[9] */
#define SCU_PINMUX_SD_VOLT0 (P1_8)  /* GPIO1[1] */
#define SCU_PINMUX_SD_DAT0  (P1_9)  /* GPIO1[2] */
#define SCU_PINMUX_SD_DAT1  (P1_10) /* GPIO1[3] */
#define SCU_PINMUX_SD_DAT2  (P1_11) /* GPIO1[4] */
#define SCU_PINMUX_SD_DAT3  (P1_12) /* GPIO1[5] */
#define SCU_PINMUX_SD_CD    (P1_13) /* GPIO1[6] */

#define SCU_PINMUX_U0_TXD   (P2_0)  /* GPIO5[0] */
#define SCU_PINMUX_U0_RXD   (P2_1)  /* GPIO5[1] */

#define SCU_PINMUX_ISP      (P2_7)  /* GPIO0[7] */

#define SCU_PINMUX_GP_CLKIN	(P4_7)

typedef enum {
	TRANSCEIVER_MODE_OFF = 0,
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#endif

typedef enum {
	LED1 = 0,
	LED2 = 1,
	LED3 = 2,
	LED4 = 3,
} led_t;

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
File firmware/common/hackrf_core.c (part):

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static struct gpio_t gpio_vaa_disable		= GPIO(2, 9);
#endif
#ifdef RAD1O
static struct gpio_t gpio_vaa_enable		= GPIO(2, 9);
#endif

static struct gpio_t gpio_w25q80bv_hold		= GPIO(1, 14);
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#ifdef HACKRF_ONE
static struct gpio_t gpio_hp				= GPIO(2,  0);
static struct gpio_t gpio_lp				= GPIO(2, 10);
static struct gpio_t gpio_tx_mix_bp			= GPIO(2, 11);
static struct gpio_t gpio_no_mix_bypass		= GPIO(1,  0);
static struct gpio_t gpio_rx_mix_bp			= GPIO(2, 12);
static struct gpio_t gpio_tx_amp			= GPIO(2, 15);
static struct gpio_t gpio_tx				= GPIO(5, 15);
static struct gpio_t gpio_mix_bypass		= GPIO(5, 16);
static struct gpio_t gpio_rx				= GPIO(5,  5);
static struct gpio_t gpio_no_tx_amp_pwr		= GPIO(3,  5);
static struct gpio_t gpio_amp_bypass		= GPIO(0, 14);
static struct gpio_t gpio_rx_amp			= GPIO(1, 11);
static struct gpio_t gpio_no_rx_amp_pwr		= GPIO(1, 12);
#endif
#ifdef RAD1O
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static struct gpio_t gpio_mixer_en			= GPIO(5,  16);
static struct gpio_t gpio_low_high_filt		= GPIO(2,  11);
static struct gpio_t gpio_low_high_filt_n	= GPIO(2,  12);
static struct gpio_t gpio_tx_amp			= GPIO(2,  15);
static struct gpio_t gpio_rx_lna			= GPIO(5,  15);
#endif

/* CPLD JTAG interface GPIO pins */
static struct gpio_t gpio_cpld_tdo			= GPIO(5, 18);
static struct gpio_t gpio_cpld_tck			= GPIO(3,  0);
#if (defined HACKRF_ONE || defined RAD1O)
static struct gpio_t gpio_cpld_tms			= GPIO(3,  4);
static struct gpio_t gpio_cpld_tdi			= GPIO(3,  1);
#else
static struct gpio_t gpio_cpld_tms			= GPIO(3,  1);
static struct gpio_t gpio_cpld_tdi			= GPIO(3,  4);
#endif

static struct gpio_t gpio_hw_sync_enable = GPIO(5,12);
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#ifdef HACKRF_ONE
	.gpio_hp = &gpio_hp,
	.gpio_lp = &gpio_lp,
	.gpio_tx_mix_bp = &gpio_tx_mix_bp,
	.gpio_no_mix_bypass = &gpio_no_mix_bypass,
	.gpio_rx_mix_bp = &gpio_rx_mix_bp,
	.gpio_tx_amp = &gpio_tx_amp,
	.gpio_tx = &gpio_tx,
	.gpio_mix_bypass = &gpio_mix_bypass,
	.gpio_rx = &gpio_rx,
	.gpio_no_tx_amp_pwr = &gpio_no_tx_amp_pwr,
	.gpio_amp_bypass = &gpio_amp_bypass,
	.gpio_rx_amp = &gpio_rx_amp,
	.gpio_no_rx_amp_pwr = &gpio_no_rx_amp_pwr,
#endif
#ifdef RAD1O
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	.gpio_mixer_en = &gpio_mixer_en,
	.gpio_low_high_filt = &gpio_low_high_filt,
	.gpio_low_high_filt_n = &gpio_low_high_filt_n,
	.gpio_tx_amp = &gpio_tx_amp,
	.gpio_rx_lna = &gpio_rx_lna,
#endif
};

jtag_gpio_t jtag_gpio_cpld = {
	.gpio_tms = &gpio_cpld_tms,
	.gpio_tck = &gpio_cpld_tck,
	.gpio_tdi = &gpio_cpld_tdi,
	.gpio_tdo = &gpio_cpld_tdo,
};

jtag_t jtag_cpld = {
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	/* MS0/CLK1 is the source for the CPLD (CODEC_X2_CLK). */
	si5351c_configure_multisynth(&clock_gen, 1, 0, 0, 0, 0);//p1 doesn't matter

	/* MS0/CLK2 is the source for SGPIO (CODEC_X2_CLK) */
	si5351c_configure_multisynth(&clock_gen, 2, 0, 0, 0, 0);//p1 doesn't matter

	return true;
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	/* MS0/CLK1 is the source for the CPLD (CODEC_X2_CLK). */
	si5351c_configure_multisynth(&clock_gen, 1, p1, 0, 1, 0);//p1 doesn't matter

	/* MS0/CLK2 is the source for SGPIO (CODEC_X2_CLK) */
	si5351c_configure_multisynth(&clock_gen, 2, p1, 0, 1, 0);//p1 doesn't matter

	return true;
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	 * Clocks:
	 *   CLK0 -> MAX5864/CPLD
	 *   CLK1 -> CPLD
	 *   CLK2 -> SGPIO
	 *   CLK3 -> External Clock Output (power down at boot)
	 *   CLK4 -> RFFC5072 (MAX2837 on rad1o)
	 *   CLK5 -> MAX2837 (MAX2871 on rad1o)
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	scu_pinmux(SCU_PINMUX_CPLD_TMS, SCU_GPIO_NOPULL | SCU_CONF_FUNCTION0);
	scu_pinmux(SCU_PINMUX_CPLD_TDI, SCU_GPIO_NOPULL | SCU_CONF_FUNCTION0);
	
	gpio_input(&gpio_cpld_tdo);
	gpio_input(&gpio_cpld_tck);
	gpio_input(&gpio_cpld_tms);
	gpio_input(&gpio_cpld_tdi);
	
	/* Configure SCU Pin Mux as GPIO */
	scu_pinmux(SCU_PINMUX_LED1, SCU_GPIO_NOPULL);
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
#ifdef RAD1O
	/* Configure RF power supply (VAA) switch control signal as output */
	gpio_output(&gpio_vaa_enable);

	/* Safe state: start with VAA turned off: */
	disable_rf_power();

	/* Disable unused clock outputs. They generate noise. */
	scu_pinmux(CLK0, SCU_CLK_IN | SCU_CONF_FUNCTION7);
	scu_pinmux(CLK2, SCU_CLK_IN | SCU_CONF_FUNCTION7);

	scu_pinmux(SCU_PINMUX_GPIO3_10, SCU_GPIO_PDN | SCU_CONF_FUNCTION0);
	scu_pinmux(SCU_PINMUX_GPIO3_11, SCU_GPIO_PDN | SCU_CONF_FUNCTION0);
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
#ifdef RAD1O
void enable_rf_power(void) {
	gpio_set(&gpio_vaa_enable);
}

void disable_rf_power(void) {
	gpio_clear(&gpio_vaa_enable);
}
#endif

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
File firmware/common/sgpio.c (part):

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}

/*
 SGPIO0 to 7 = DAC/ADC data bits 0 to 7 (Nota: DAC is 10bits but only bit9 to bit2 are used bit1 & 0 are forced to 0 by CPLD)
 ADC=> CLK x 2=CLKx2 with CLKx2(0)rising=D0Q, CLKx2(1)rising=D1I (corresponds to CLK(0)falling+tD0Q=>D0Q, CLK(1)rising+tDOI=>D1I, CLK(1)falling+tD0Q=>D1Q, CLK(1)rising+tDOI=>D2I ...)
 tDOI(CLK Rise to I-ADC Channel-I Output Data Valid)=7.4 to 9ns, tD0Q(CLK Fall to Q-ADC Channel-Q Output Data Valid)=6.9 to 9ns
 DAC=> CLK x 2=CLKx2 with CLKx2(0)rising=Q:N-2, CLKx2(1)rising=I:N-1(corresponds to CLK(0)rising=>Q:N-2, CLK(0)falling I:N-1, CLK(1)rising=>Q:N-1, CLK(1)falling I:N ...)
 tDSI(I-DAC Data to CLK Fall Setup Time)=min 10ns, tDSQ(Q-DAC Data to CLK Rise Setup Time)=min 10ns
 
 SGPIO8 Clock Input (External Clock)
 SGPIO9 Capture Input (Capture/ChipSelect, 1=Enable Capture, 0=Disable capture)
 SGPIO10 Disable Output (1/High=Disable codec data stream, 0/Low=Enable codec data stream)
 SGPIO11 Direction Output (1/High=TX mode LPC43xx=>CPLD=>DAC, 0/Low=RX mode LPC43xx<=CPLD<=ADC)
*/
void sgpio_configure(
	sgpio_config_t* const config,
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	const uint_fast8_t cpld_direction =
		(direction == SGPIO_DIRECTION_TX) ? 1 : 0;
    SGPIO_GPIO_OUTREG =
          (cpld_direction << 11) /* 1=Output SGPIO11 High(TX mode), 0=Output SGPIO11 Low(RX mode)*/
        | (1L << 10)	// disable codec data stream during configuration (Output SGPIO10 High)
		;

#ifdef RAD1O
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		? (0xFF << 0)
		: (0x00 << 0);
	SGPIO_GPIO_OENREG =
	      (1L << 14)	// GPDMA burst request SGPIO14 active
	    | (1L << 11)	// direction output SGPIO11 active 
	    | (1L << 10)	// disable output SGPIO10 active
	    | (0L <<  9)	// capture input SGPIO9 (output i is tri-stated)
	    | (0L <<  8)	// clock input SGPIO8 (output i is tri-stated)
        | sgpio_gpio_data_direction // 0xFF=Output all SGPIO High(TX mode), 0x00=Output all SPGIO Low(RX mode)
		;
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		  SGPIO_OUT_MUX_CFG_P_OE_CFG(0) /* 0x0 gpio_oe (state set by GPIO_OEREG) */
		| SGPIO_OUT_MUX_CFG_P_OUT_CFG(0) /* 0x0 dout_doutm1 (1-bit mode) */ 
		;
	SGPIO_OUT_MUX_CFG( 9) =		// SGPIO9: Input: qualifier
		  SGPIO_OUT_MUX_CFG_P_OE_CFG(0) /* 0x0 gpio_oe (state set by GPIO_OEREG) */
		| SGPIO_OUT_MUX_CFG_P_OUT_CFG(0) /* 0x0 dout_doutm1 (1-bit mode) */
		;
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		  SGPIO_OUT_MUX_CFG_P_OE_CFG(0) /* 0x0 gpio_oe (state set by GPIO_OEREG) */
		| SGPIO_OUT_MUX_CFG_P_OUT_CFG(4) /* 0x4=gpio_out (level set by GPIO_OUTREG) */
		;
	SGPIO_OUT_MUX_CFG(14) =		// SGPIO14: Output: internal GPDMA burst request
		  SGPIO_OUT_MUX_CFG_P_OE_CFG(0) /* 0x4 dout_oem1 (1-bit mode) */
		| SGPIO_OUT_MUX_CFG_P_OUT_CFG(0) /* 0x0 dout_doutm1 (1-bit mode) */
		;

	const uint_fast8_t output_multiplexing_mode =
		config->slice_mode_multislice ? 11 : 9;
	/* SGPIO0 to SGPIO7 */
	for(uint_fast8_t i=0; i<8; i++) {
		// SGPIO pin 0 outputs slice A bit "i".
		SGPIO_OUT_MUX_CFG(i) =
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		      SGPIO_MUX_CFG_CONCAT_ORDER(concat_order)
		    | SGPIO_MUX_CFG_CONCAT_ENABLE(concat_enable)
		    | SGPIO_MUX_CFG_QUALIFIER_SLICE_MODE(0) /* Select qualifier slice A(0x0) */
		    | SGPIO_MUX_CFG_QUALIFIER_PIN_MODE(1) /* Select qualifier pin SGPIO9(0x1) */
		    | SGPIO_MUX_CFG_QUALIFIER_MODE(3) /* External SGPIO */
		    | SGPIO_MUX_CFG_CLK_SOURCE_SLICE_MODE(0) /* Select clock source slice D(0x0) */
		    | SGPIO_MUX_CFG_CLK_SOURCE_PIN_MODE(0) /* Source Clock Pin 0x0 = SGPIO8 */
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			  SGPIO_MUX_CFG_CONCAT_ORDER(0) /* Self-loop */
			| SGPIO_MUX_CFG_CONCAT_ENABLE(1)
			| SGPIO_MUX_CFG_QUALIFIER_SLICE_MODE(0) /* Select qualifier slice A(0x0) */
			| SGPIO_MUX_CFG_QUALIFIER_PIN_MODE(1) /* Select qualifier pin SGPIO9(0x1) */
			| SGPIO_MUX_CFG_QUALIFIER_MODE(3) /* External SGPIO */
			| SGPIO_MUX_CFG_CLK_SOURCE_SLICE_MODE(0) /* Select clock source slice D(0x0) */
			| SGPIO_MUX_CFG_CLK_SOURCE_PIN_MODE(0) /* Source Clock Pin 0x0 = SGPIO8 */
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void sgpio_cpld_stream_enable(sgpio_config_t* const config) {
	(void)config;
	// Enable codec data stream.
	SGPIO_GPIO_OUTREG &= ~(1L << 10); /* SGPIO10 */
}

void sgpio_cpld_stream_disable(sgpio_config_t* const config) {
	(void)config;
	// Disable codec data stream.
	SGPIO_GPIO_OUTREG |= (1L << 10); /* SGPIO10 */
}

bool sgpio_cpld_stream_is_enabled(sgpio_config_t* const config) {
	(void)config;
	return (SGPIO_GPIO_OUTREG & (1L << 10)) == 0; /* SGPIO10 */
}


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/* Called when TX/RX changes od sgpio_cpld_stream_rx_set_q_invert
 * gets called. */
static void update_q_invert(sgpio_config_t* const config) {
	/* 1=Output SGPIO11 High(TX mode), 0=Output SGPIO11 Low(RX mode) */
	bool tx_mode = (SGPIO_GPIO_OUTREG & (1 << 11)) > 0;

	/* 0.13: P1_18 */
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
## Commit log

2019-01-10 Move RF section around to make room for protection (yet to be added)
2019-01-11 Corrected libraries (to use gsg-kicad-lib) and added SMP1330 protection
2019-01-17 Improved RF layout by passing signals through protection devices instead of using stubs
2020-01-30 Clean up the CMake build system and improve the FindFFTW3 module.
2020-01-30 Update host build README for new CMake changes (esp. Windows)
2020-01-30 Fixes for Linux build
2020-01-30 Couple more fixes for MSVC, also add new FindMath module
2020-01-30 Include winsock.h to get struct timeval
2020-01-30 Try to fix Travis OS X build error
2020-01-30 Add docs about pthread-win32
2020-01-30 Travis rebuild bump
2020-01-30 Whoops, AppVeyor caught a bug in FindFFTW where the includes not being found weren't generating a fatal error.
2020-01-30 Invert Windows preprocessor flag so it's only needed when using a static build. This preserves compatibility with the previous system.
2020-01-30 One more fix: replace hardcoded include paths with a PATH_SUFFIX to standard include paths
2020-01-30 Fix copy-paste error
